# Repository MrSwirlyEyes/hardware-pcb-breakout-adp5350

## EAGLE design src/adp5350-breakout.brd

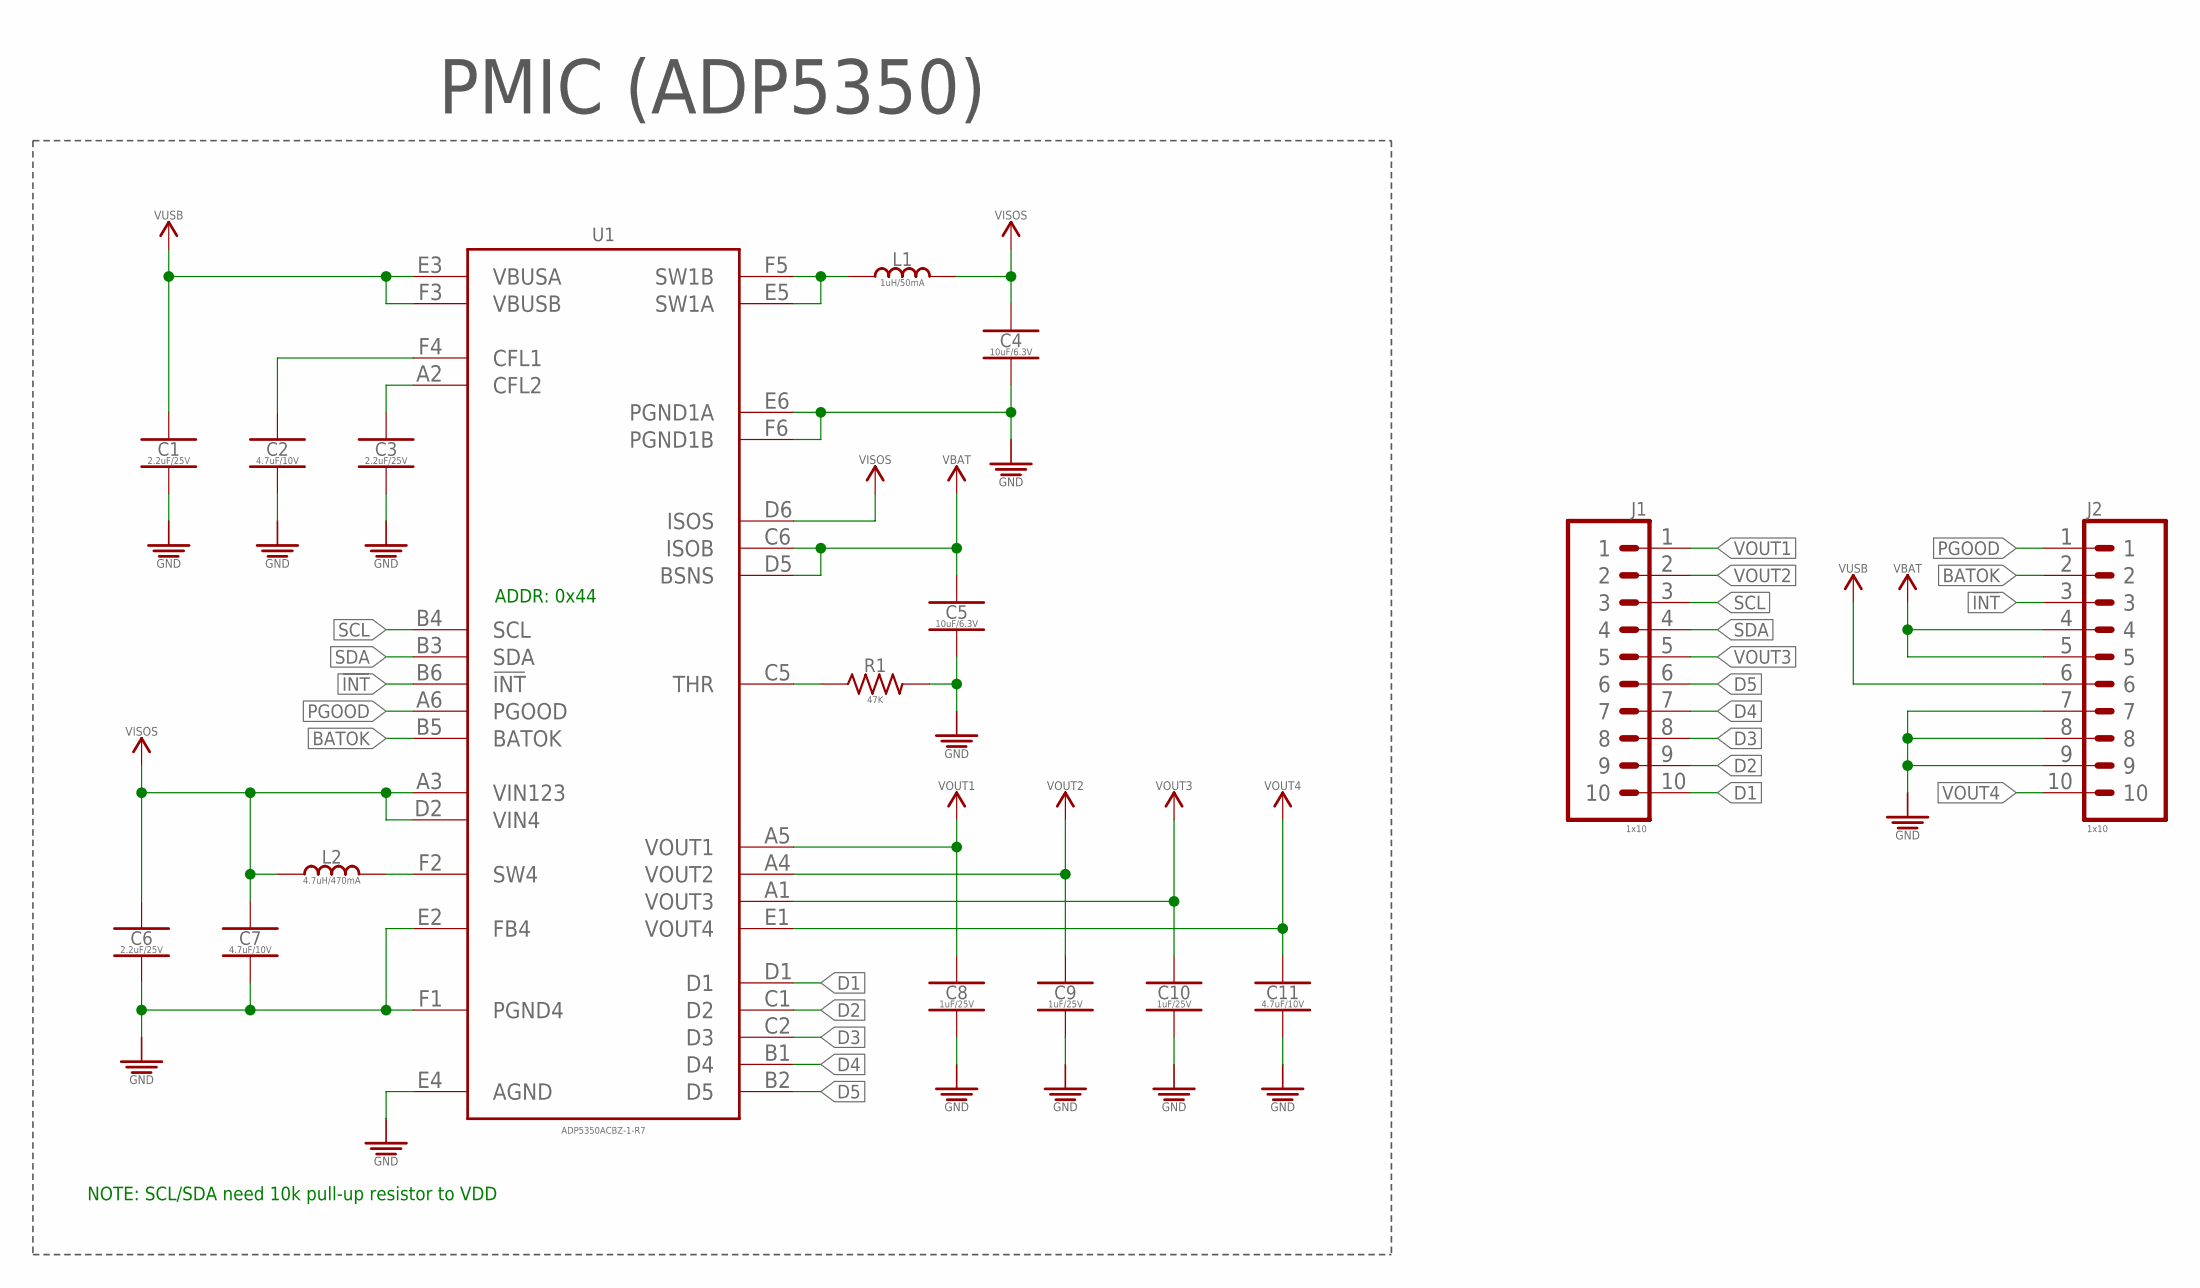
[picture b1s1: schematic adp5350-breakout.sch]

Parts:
C1, C3, C6: 2.2uF/25V; CAPC1005X55_SMD-0402
C2, C7, C11: 4.7uF/10V; CAPC1005X55_SMD-0402
C4, C5: 10uF/6.3V; CAPC1005X55_SMD-0402
C8, C9, C10: 1uF/25V; CAPC1005X55_SMD-0402
J1, J2: 1x10; HDRV10W64P254_1X10_2540X254X838B
L1: 1uH/50mA; INDC1608X60-0603
L2: 4.7uH/470mA; INDC1608X60-0603
R1: 47K; RESC1005X35_SMD-0402
U1: ADP5350ACBZ-1-R7; BGA36C50P6X6_331X336X66N

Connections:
!INT!: J2.3, U1.B6 (!INT!)
BATOK: J2.2, U1.B5 (BATOK)
D1: J1.10, U1.D1
D2: J1.9, U1.C1 (D2)
D3: J1.8, U1.C2 (D3)
D4: J1.7, U1.B1 (D4)
D5: J1.6, U1.B2 (D5)
GND: C1.2, C2.2, C3.2, C4.2, C5.2, C6.2, C7.2, C8.2, C9.2, C10.2, C11.2, J2.7, J2.8, J2.9, R1.2, U1.E2 (FB4), U1.E4 (AGND), U1.E6 (PGND1A), U1.F1 (PGND4), U1.F6 (PGND1B)
unnamed: C3.1, U1.A2 (CFL2)
unnamed: C2.1, U1.F4 (CFL1)
unnamed: L2.2, U1.F2 (SW4)
unnamed: L1.1, U1.E5 (SW1A), U1.F5 (SW1B)
unnamed: R1.1, U1.C5 (THR)
PGOOD: J2.1, U1.A6 (PGOOD)
SCL: J1.3, U1.B4 (SCL)
SDA: J1.4, U1.B3 (SDA)
VBAT: C5.1, J2.4, J2.5, U1.C6 (ISOB), U1.D5 (BSNS)
VISOS: C4.1, C6.1, C7.1, L1.2, L2.1, U1.A3 (VIN123), U1.D2 (VIN4), U1.D6 (ISOS)
VOUT1: C8.1, J1.1, U1.A5 (VOUT1)
VOUT2: C9.1, J1.2, U1.A4 (VOUT2)
VOUT3: C10.1, J1.5, U1.A1 (VOUT3)
VOUT4: C11.1, J2.10, U1.E1 (VOUT4)
VUSB: C1.1, J2.6, U1.E3 (VBUSA), U1.F3 (VBUSB)

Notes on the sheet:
PMIC (ADP5350)
NOTE: SCL/SDA need 10k pull-up resistor to VDD
ADDR: 0x44

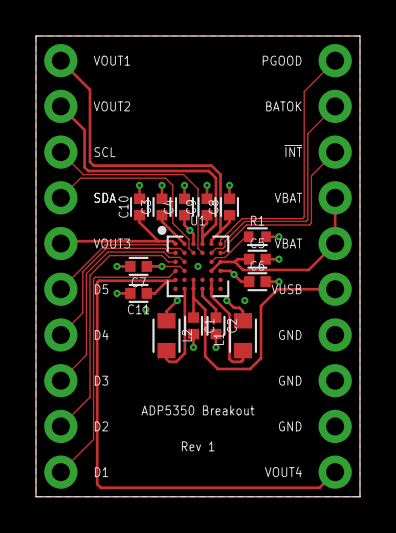
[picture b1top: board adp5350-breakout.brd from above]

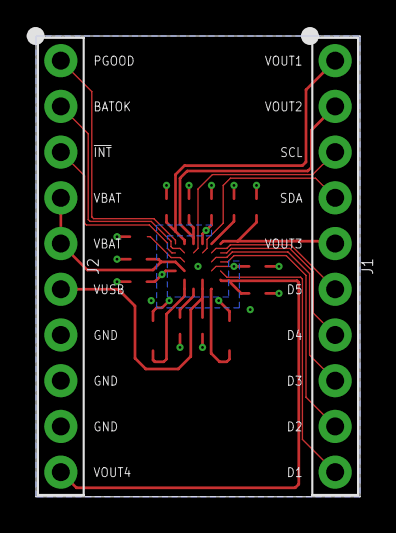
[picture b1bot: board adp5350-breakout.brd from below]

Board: 2 copper layers, 18.0 x 25.6 mm, 17 parts (2 on the bottom side), 23 nets.

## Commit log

2021-01-12 [Rev 1] - Initialize repo.
2021-08-11 Update CAM files.
